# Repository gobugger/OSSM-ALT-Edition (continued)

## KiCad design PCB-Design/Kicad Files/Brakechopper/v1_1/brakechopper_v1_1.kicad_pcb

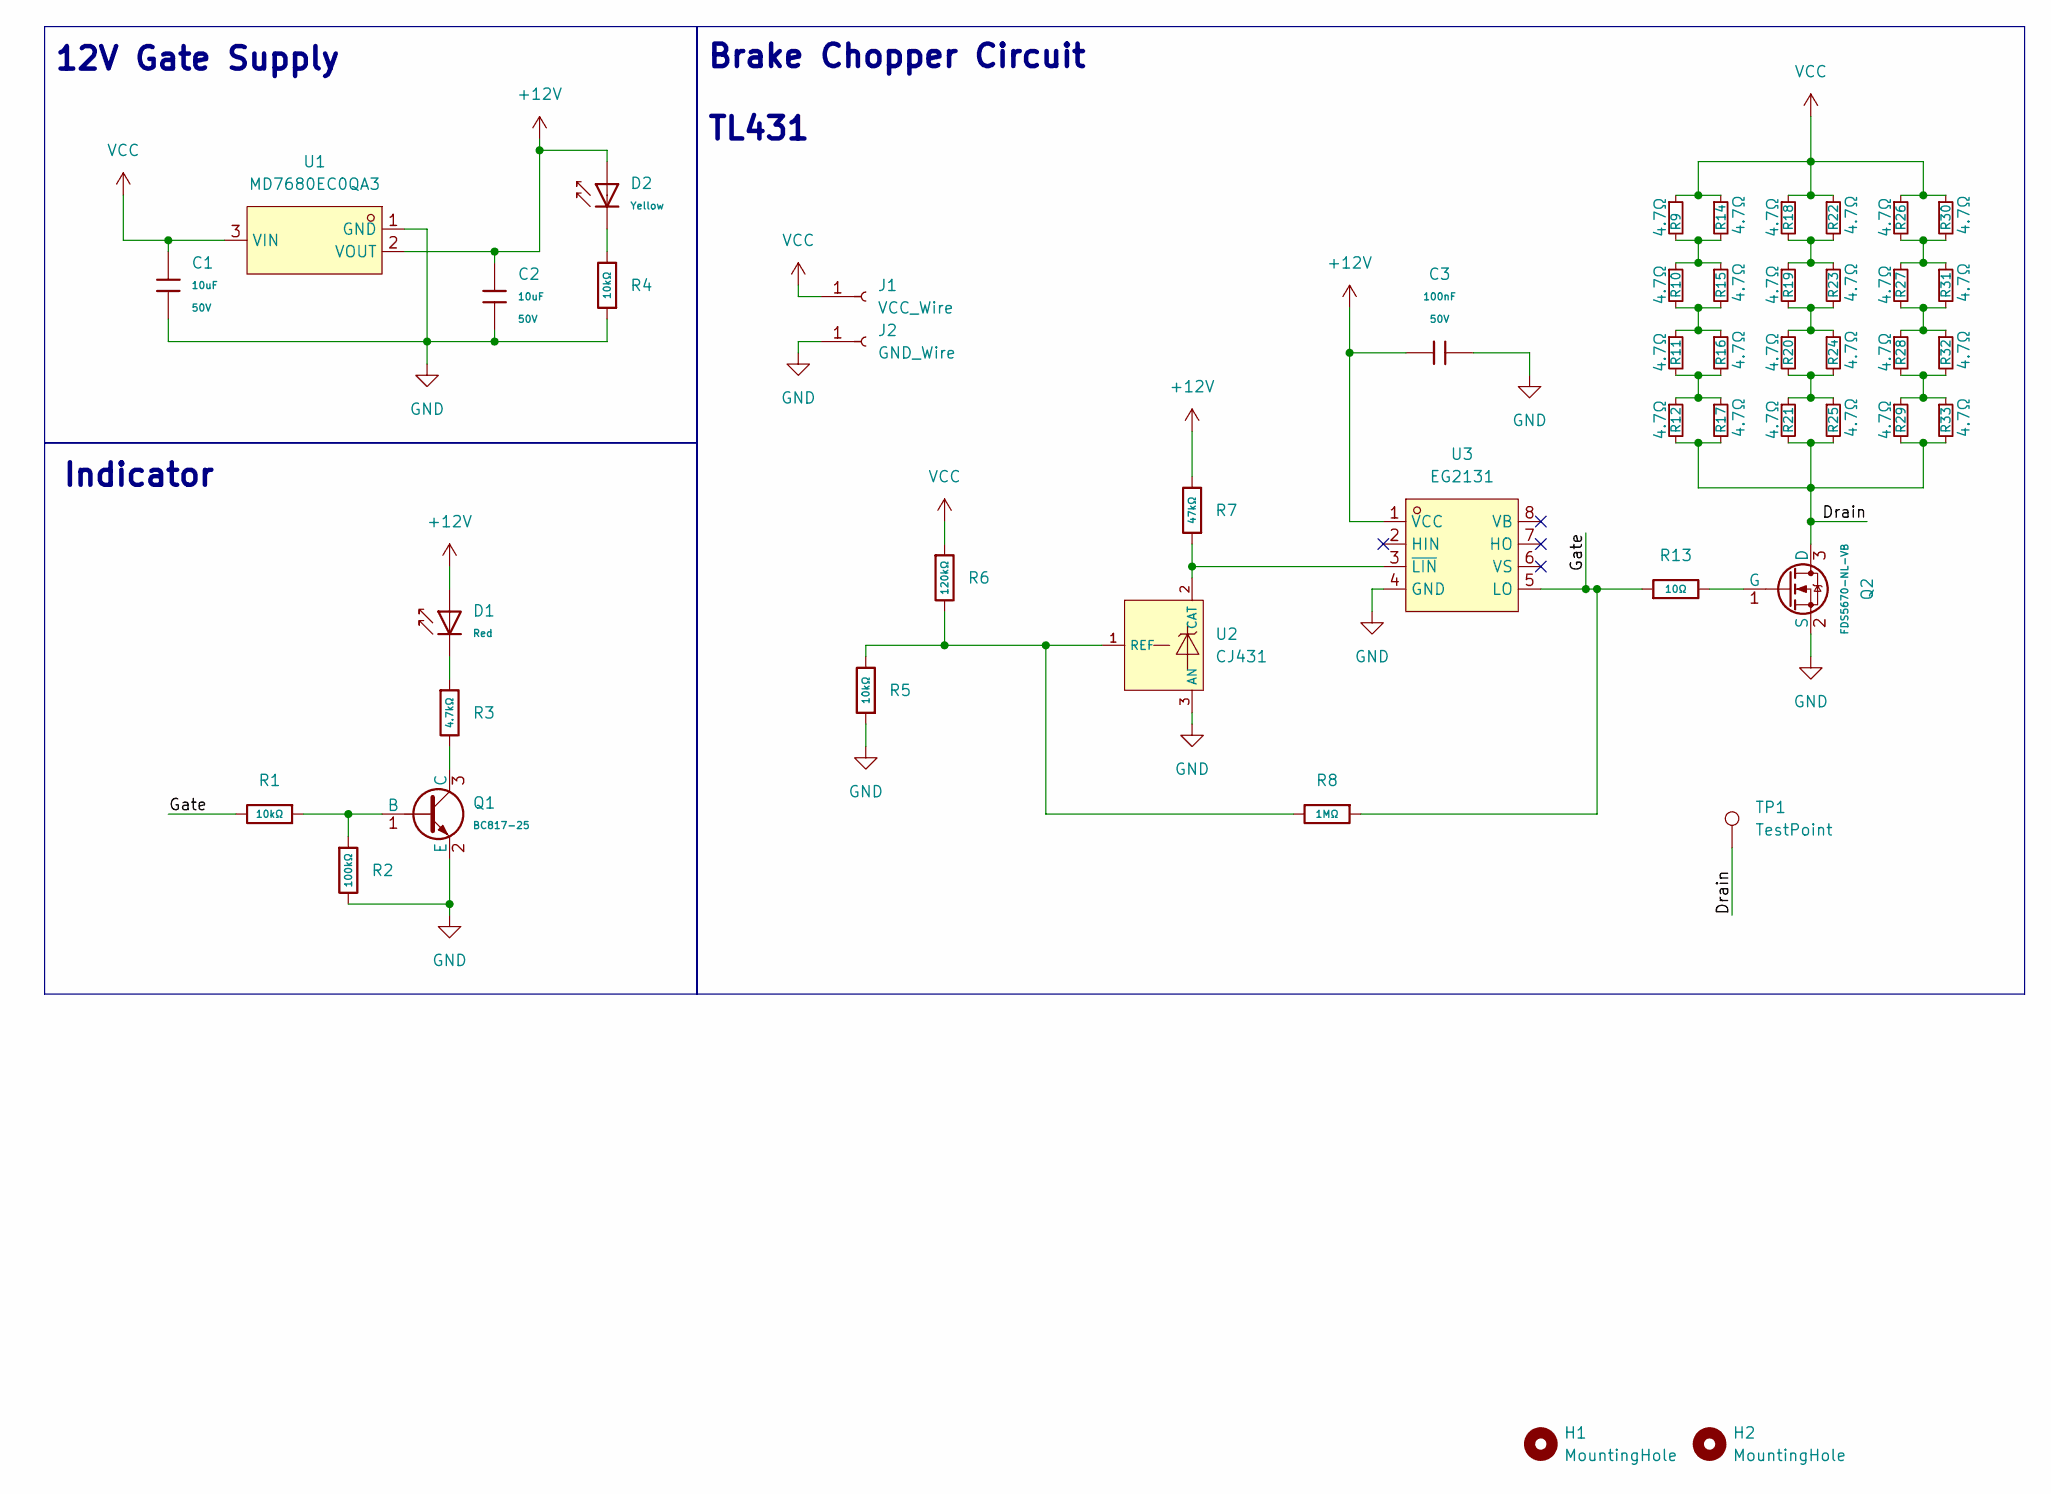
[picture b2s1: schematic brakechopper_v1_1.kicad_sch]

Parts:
C1, C2: 10uF; C_0805; Voltage Rated 50V; Tolerance ±10%; Part GRM21BR61H106KE43L; LCSC C440198
C3: 100nF; C_0603; Voltage Rated 50V; Tolerance ±10%; Part CC0603KRX7R9BB104; LCSC C14663
D1: Red; D_0603; Part KT-0603R; LCSC C2286
D2: Yellow; D_0603; Forward Voltage (VF) 1.6V~2.6V; Part NCD0603Y2; LCSC C89811
H1, H2: MountingHole; MountingHole_2.2mm_M2_ISO14580
J1: VCC_Wire; Solder_Wire_PowerPort_VCC
J2: GND_Wire; Solder_Wire_PowerPort_GND
Q1: BC817-25; Q_SOT-23; Part BC817-25; LCSC C20069154
Q2: FDS5670-NL-VB; SO-8 N-channel mosfet FDS5351; Part 2N7002; LCSC C5878792
R1, R4, R5: 10kΩ; R_0603; Overload Voltage (Max) 75V; Tolerance ±1%; Part 0603WAF1002T5E; LCSC C25804
R2: 100kΩ; R_0603; Overload Voltage (Max) 75V; Tolerance ±1%; Part 0603WAF1003T5E; LCSC C25803
R3: 4.7kΩ; R_0603; Overload Voltage (Max) 75V; Tolerance ±1%; Part 0603WAF4701T5E; LCSC C23162
R6: 120kΩ; R_0603; Overload Voltage (Max) 75V; Tolerance ±1%; Part 0603WAF1203T5E; LCSC C25808
R7: 47kΩ; R_0603; Overload Voltage (Max) 75V; Tolerance ±1%; Part 0603WAF4702T5E; LCSC C25819
R8: 1MΩ; R_0603; Overload Voltage (Max) 75V; Tolerance ±1%; Part 0603WAF1004T5E; LCSC C22935
R9, R10, R11, R12, R14, R15, R16, R17, R18, R19, R20, R21, R22, R23, R24, R25, R26, R27, R28, R29, R30, R31, R32, R33: 4.7Ω; R_1218_3246Metric_Pad1.22x4.75mm_HandSolder; LCSC C876073
R13: 10Ω; R_0603; Overload Voltage (Max) 75V; Tolerance ±1%; Part 0603WAF100JT5E; LCSC C22859
TP1: TestPoint; TestPoint_Pad_D1.0mm
U1: MD7680EC0QA3; SOT-23-3L_L2.9-W1.6-P1.90-LS2.8-BL; LCSC Part C42377927
U2: CJ431; SOT-23-3_L2.9-W1.6-P1.90-LS2.8-BR; Output Voltage 2.5V~36V; Tolerance ±0.5%; Part CJ431; LCSC C3113
U3: EG2131; SOP-8_L4.9-W3.9-P1.27-LS6.0-BL; LCSC Part C5240691

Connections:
+12V: C2.2, C3.1, D1.2, D2.2, R7.2, U1.2 (VOUT), U3.1 (VCC)
/Drain: Q2.3 (D), R12.2, R17.2, R21.2, R25.2, R29.2, R33.2, TP1.1 (1_1)
/Gate: R1.2, R8.1, R13.1, U3.5 (LO)
GND: C1.1, C2.1, C3.2, J2.1 (Pin_1_1), Q1.2 (E), Q2.2 (S), R2.2, R4.1, R5.1, U1.1 (GND), U2.3 (AN), U3.4 (GND)
unnamed: D1.1, R3.1
unnamed: D2.1, R4.2
unnamed: Q1.1 (B), R1.1, R2.1
unnamed: Q1.3 (C), R3.2
unnamed: Q2.1 (G), R13.2
unnamed: R9.2, R10.1, R14.2, R15.1
unnamed: R10.2, R11.1, R15.2, R16.1
unnamed: R11.2, R12.1, R16.2, R17.1
unnamed: R18.2, R19.1, R22.2, R23.1
unnamed: R19.2, R20.1, R23.2, R24.1
unnamed: R20.2, R21.1, R24.2, R25.1
unnamed: R26.2, R27.1, R30.2, R31.1
unnamed: R27.2, R28.1, R31.2, R32.1
unnamed: R28.2, R29.1, R32.2, R33.1
unnamed: R7.1, U2.2 (CAT), U3.3 (~LIN)
unnamed: R5.2, R6.2, R8.2, U2.1 (REF)
VCC: C1.2, J1.1 (Pin_1_1), R6.1, R9.1, R14.1, R18.1, R22.1, R26.1, R30.1, U1.3 (VIN)

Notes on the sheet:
Indicator
Brake Chopper Circuit TL431
12V Gate Supply

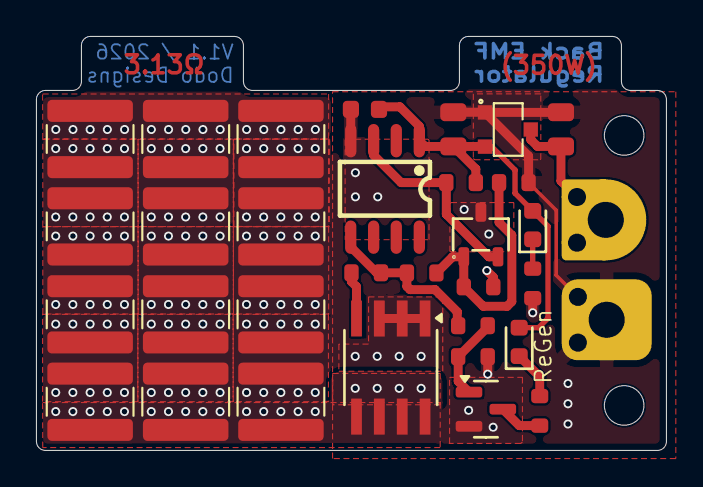
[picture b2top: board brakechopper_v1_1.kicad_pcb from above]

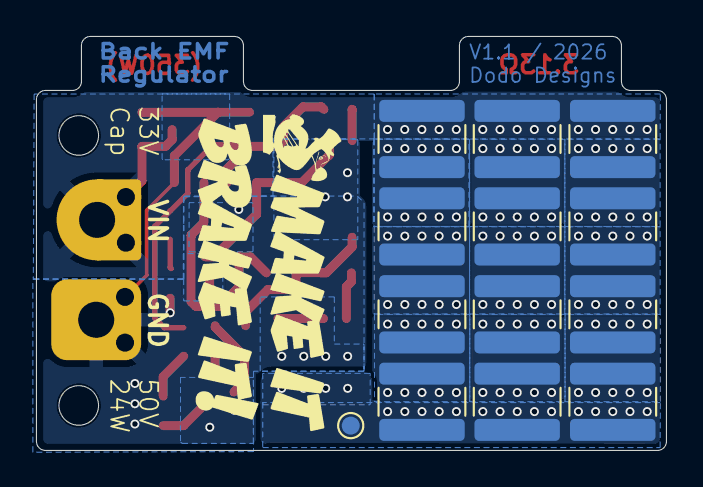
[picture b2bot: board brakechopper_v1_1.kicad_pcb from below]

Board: 2 copper layers, 35.0 x 23.0 mm, 48 parts (13 on the bottom side), 21 nets.

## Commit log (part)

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2025-12-11 Fixed Tolerances after testing with different printers
2025-12-14 license
2025-12-16 power information
2025-12-16 bom update
2025-12-16 fixed links
2025-12-16 remove folder
2025-12-16 small fixes
2025-12-22 MGN12 Mounts / assembly
2026-01-09 better attributin'
2026-01-11 Version 1 Print Release
2026-01-11 PCB folder info
2026-03-09 release 0.9
2026-03-09 teaser added
2026-03-16 minor tolerance fix
2026-04-04 updated power adapters
    updated list
2026-04-04 Updated Power List
    Added Apple 67W adapter.
